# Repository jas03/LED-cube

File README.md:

# LED-cube
Design project for ECE-411

A 3x3x3 tricolor LED Cube that responds to music.

Members:

Evan Yand
Matthew Konyndyk
Alex Mendez
Jasjit Singh

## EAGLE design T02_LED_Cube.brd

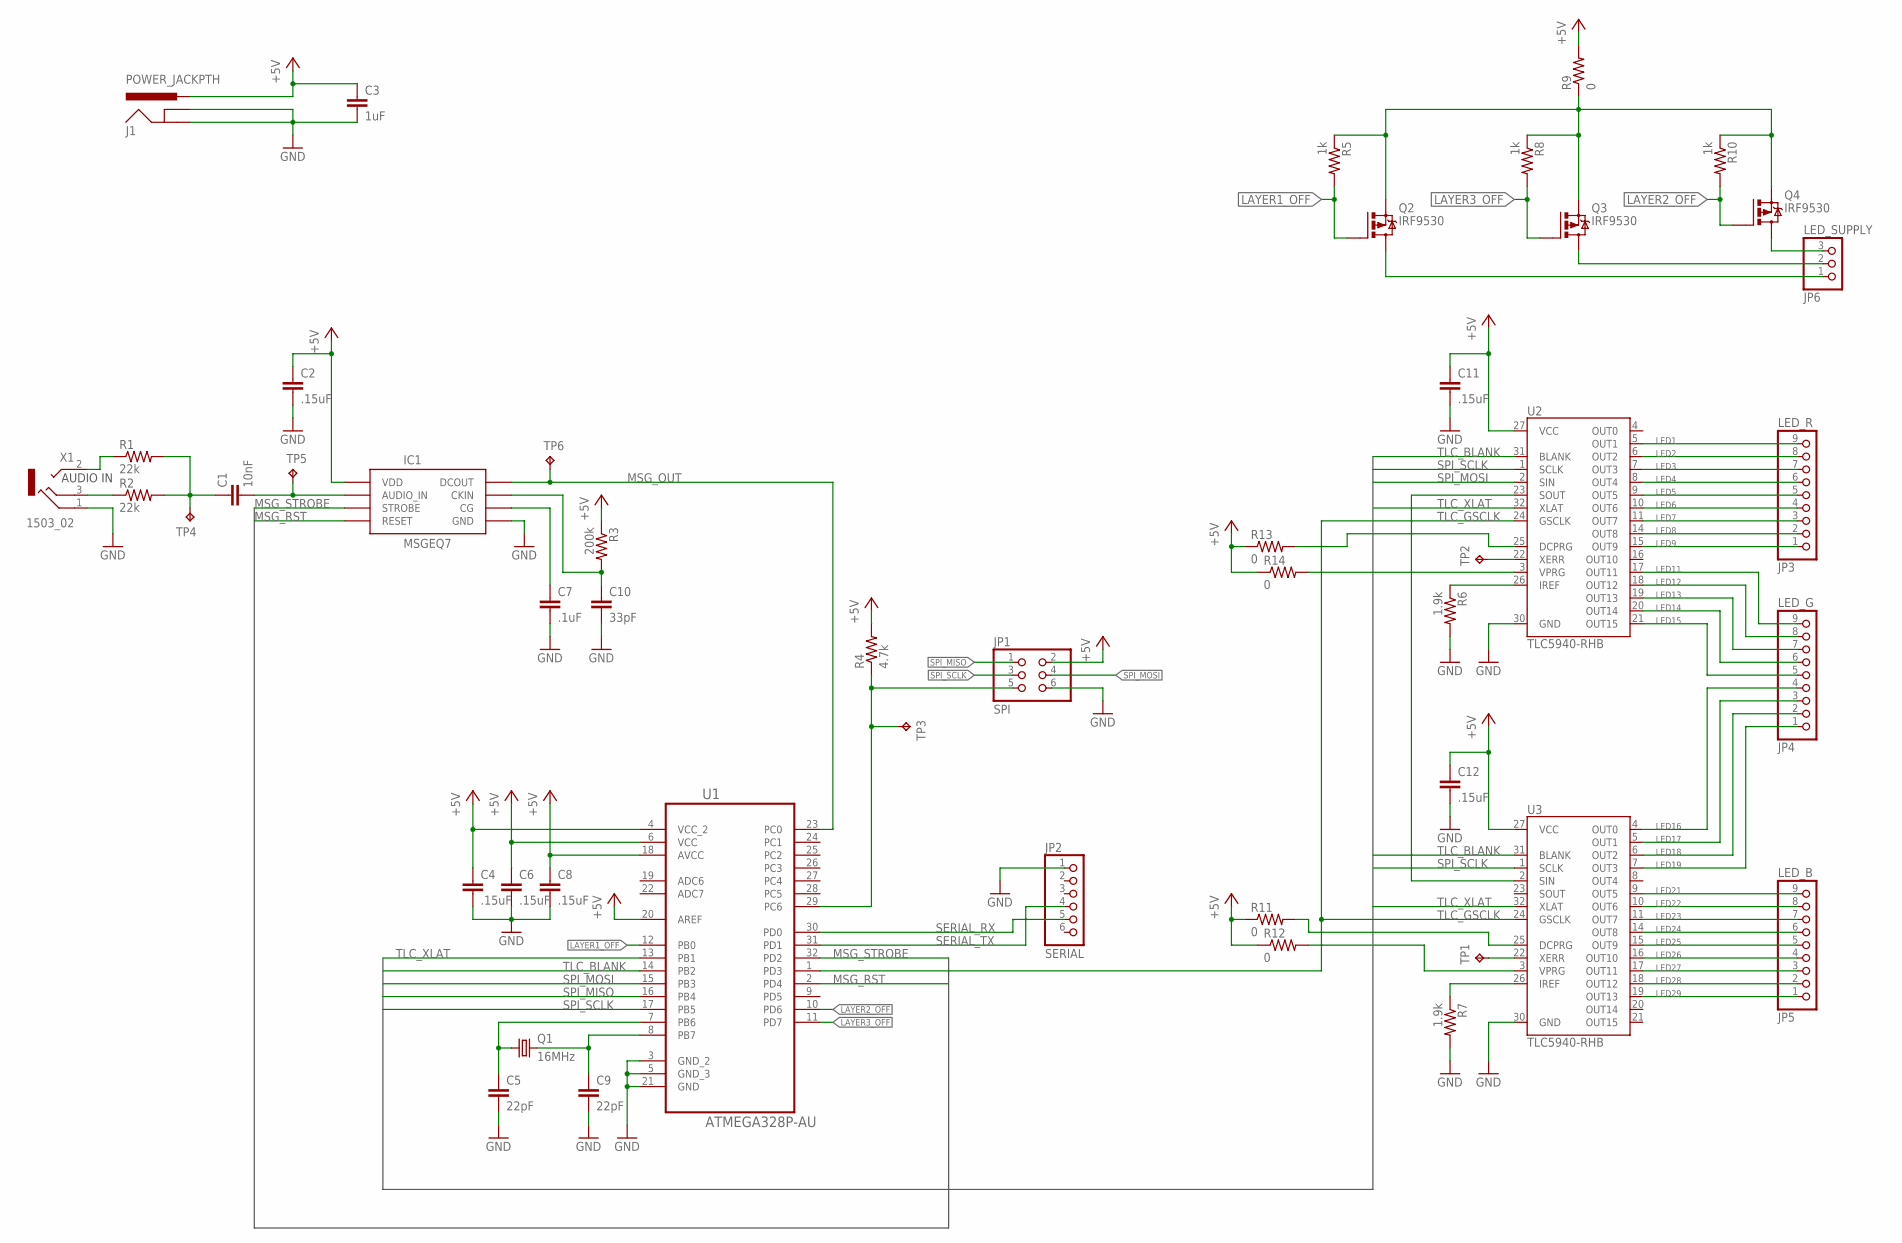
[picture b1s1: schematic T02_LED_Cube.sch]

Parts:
C1: 10nF; C0805
C2, C4, C6, C8, C11, C12: .15uF; C0402
C3: 1uF; C0805
C5, C9: 22pF; C0805
C7: .1uF; C0805
C10: 33pF; C0805
IC1: MSGEQ7SOIC; SOIC8
J1: POWER_JACKPTH; POWER_JACK_PTH
JP1: SPI; 2X03
JP2: SERIAL; 1X06
JP3: LED_R; 1X09
JP4: LED_G; 1X09
JP5: LED_B; 1X09
JP6: LED_SUPPLY; 1X03
Q1: 16MHz; HC49UP
Q2, Q3, Q4: IRF9530; TO220BV
R1, R2: 22k; R0805
R3: 200k; R0805
R4: 4.7k; R0805
R5, R8, R10: 1k; R0805
R6, R7: 1.9k; R0402
R9: 0; R1210
R11, R12, R13, R14: 0; R0402
TP1, TP2, TP3, TP4, TP5, TP6: TPPAD1-13; P1-13
U1: ATMEGA328P-AU; QFP80P900X900X120-32N
U2, U3: TLC5940-RHB; QFN-32
X1: 1503_02

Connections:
+5V: C2.1, C3.1, C4.1, C6.1, C8.1, C11.1, C12.1, IC1.1 (VDD), J1.PWR, JP1.2, R3.1, R4.2, R9.2, R11.1, R12.1, R13.1, R14.1, U1.4 (VCC_2), U1.6 (VCC), U1.18 (AVCC), U1.20 (AREF), U2.27 (VCC), U3.27 (VCC)
ATM_RST: JP1.5, R4.1, TP3.TP, U1.29 (PC6)
CRY_1: C5.1, Q1.1, U1.7 (PB6)
CRY_2: C9.1, Q1.2, U1.8 (PB7)
GND: C2.2, C3.2, C4.2, C5.2, C6.2, C7.2, C8.2, C9.2, C10.2, C11.2, C12.2, IC1.2 (GND), J1.GND, J1.GNDBREAK, JP1.6, JP2.1, R6.2, R7.2, U1.3 (GND_2), U1.5 (GND_3), U1.21 (GND), U2.30 (GND), U3.30 (GND), X1.1
LAY1_SUPPLY: JP6.1, Q2.D
LAY2_SUPPLY: JP6.3, Q4.D
LAY3_SUPPLY: JP6.2, Q3.D
LAYER1_OFF: Q2.G, R5.2, U1.12 (PB0)
LAYER2_OFF: Q4.G, R10.2, U1.10 (PD6)
LAYER3_OFF: Q3.G, R8.2, U1.11 (PD7)
LED1: JP3.9, U2.5 (OUT1)
LED2: JP3.8, U2.6 (OUT2)
LED3: JP3.7, U2.7 (OUT3)
LED4: JP3.6, U2.8 (OUT4)
LED5: JP3.5, U2.9 (OUT5)
LED6: JP3.4, U2.10 (OUT6)
LED7: JP3.3, U2.11 (OUT7)
LED8: JP3.2, U2.14 (OUT8)
LED9: JP3.1, U2.15 (OUT9)
LED11: JP4.9, U2.17 (OUT11)
LED12: JP4.8, U2.18 (OUT12)
LED13: JP4.7, U2.19 (OUT13)
LED14: JP4.6, U2.20 (OUT14)
LED15: JP4.5, U2.21 (OUT15)
LED16: JP4.4, U3.4 (OUT0)
LED17: JP4.3, U3.5 (OUT1)
LED18: JP4.2, U3.6 (OUT2)
LED19: JP4.1, U3.7 (OUT3)
LED21: JP5.9, U3.9 (OUT5)
LED22: JP5.8, U3.10 (OUT6)
LED23: JP5.7, U3.11 (OUT7)
LED24: JP5.6, U3.14 (OUT8)
LED25: JP5.5, U3.15 (OUT9)
LED26: JP5.4, U3.16 (OUT10)
LED27: JP5.3, U3.17 (OUT11)
LED28: JP5.2, U3.18 (OUT12)
LED29: JP5.1, U3.19 (OUT13)
LED_SUPPLY: Q2.S, Q3.S, Q4.S, R5.1, R8.1, R9.1, R10.1
MSG_CG: C7.1, IC1.6 (CG)
MSG_CKIN: C10.1, IC1.8 (CKIN), R3.2
MSG_INPUT: C1.2, IC1.5 (AUDIO_IN), TP5.TP
MSG_OUT: IC1.3 (DCOUT), TP6.TP, U1.23 (PC0)
MSG_RST: IC1.7 (RESET), U1.2 (PD4)
MSG_STROBE: IC1.4 (STROBE), U1.32 (PD2)
unnamed: R2.1, X1.3
unnamed: R1.1, X1.2
unnamed: R12.2, U3.3 (VPRG)
unnamed: R14.2, U2.3 (VPRG)
unnamed: R11.2, U3.25 (DCPRG)
unnamed: R13.2, U2.25 (DCPRG)
SERIAL_RX: JP2.5, U1.30 (PD0)
SERIAL_TX: JP2.4, U1.31 (PD1)
SPI_MISO: JP1.1, U1.16 (PB4)
SPI_MOSI: JP1.4, U1.15 (PB3), U2.2 (SIN)
SPI_SCLK: JP1.3, U1.17 (PB5), U2.1 (SCLK), U3.1 (SCLK)
TLC1_ERR: TP2.TP, U2.22 (XERR)
TLC1_IREF: R6.1, U2.26 (IREF)
TLC2_ERR: TP1.TP, U3.22 (XERR)
TLC2_IREF: R7.1, U3.26 (IREF)
TLC_BLANK: U1.14 (PB2), U2.31 (BLANK), U3.31 (BLANK)
TLC_CHAIN: U2.23 (SOUT), U3.2 (SIN)
TLC_GSCLK: U1.1 (PD3), U2.24 (GSCLK), U3.24 (GSCLK)
TLC_XLAT: U1.13 (PB1), U2.32 (XLAT), U3.32 (XLAT)
UNFILTERED_INPUT: C1.1, R1.2, R2.2, TP4.TP

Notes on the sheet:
AUDIO IN

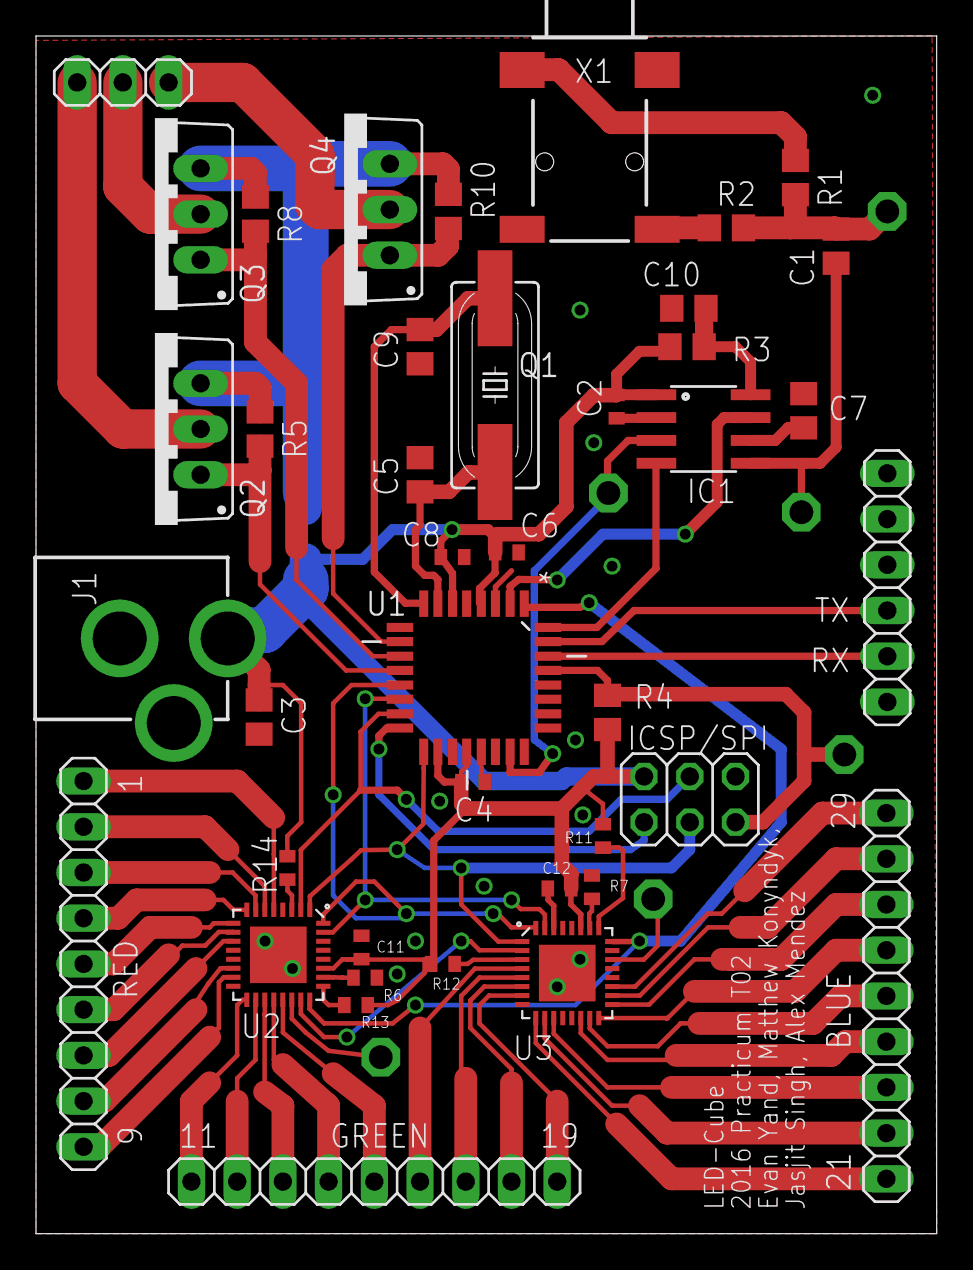
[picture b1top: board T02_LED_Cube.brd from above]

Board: 2 copper layers, 50.0 x 66.5 mm, 48 parts (1 on the bottom side), 65 nets.

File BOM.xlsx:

Part | Value | Device | Package | Description | Cost @ 500 units
Components
C1 | 10nF | C-EUC0805 | C0805 | Capacitor | 9.9000000000000008E-3
C2 | .15uF | C-EUC0402 | C0402 | Capacitor | 9.9000000000000008E-3
C3 | 1uF | C-EUC0805 | C0805 | Capacitor | 9.9000000000000008E-3
C4 | .15uF | C-EUC0402 | C0402 | Capacitor | 9.9000000000000008E-3
C5 | 22pF | C-EUC0805 | C0805 | Capacitor | 9.9000000000000008E-3
C6 | .15uF | C-EUC0402 | C0402 | Capacitor | 9.9000000000000008E-3
C7 | .1uF | C-EUC0805 | C0805 | Capacitor | 9.9000000000000008E-3
C8 | .15uF | C-EUC0402 | C0402 | Capacitor | 9.9000000000000008E-3
C9 | 22pF | C-EUC0805 | C0805 | Capacitor | 9.9000000000000008E-3
C10 | 33pF | C-EUC0805 | C0805 | Capacitor | 9.9000000000000008E-3
C11 | .15uF | C-EUC0402 | C0402 | Capacitor | 9.9000000000000008E-3
C12 | .15uF | C-EUC0402 | C0402 | Capacitor | 9.9000000000000008E-3
R1 | 22k | R-US_R0805 | R0805 | Resistor | 2.8999999999999998E-3
R2 | 22k | R-US_R0805 | R0805 | Resistor | 2.8999999999999998E-3
R3 | 200k | R-US_R0805 | R0805 | Resistor | 2.8999999999999998E-3
R4 | 4.7k | R-US_R0805 | R0805 | Resistor | 2.8999999999999998E-3
R5 | 1k | R-US_R0805 | R0805 | Resistor | 2.8999999999999998E-3
R6 | 1.9k | R-US_R0402 | R0402 | Resistor | 2.8999999999999998E-3
R7 | 1.9k | R-US_R0402 | R0402 | Resistor | 2.8999999999999998E-3
R8 | 1k | R-US_R0805 | R0805 | Resistor | 2.8999999999999998E-3
R9 | 0 | R-US_R1210 | R1210 | Resistor | 2.8999999999999998E-3
R10 | 1k | R-US_R0805 | R0805 | Resistor | 2.8999999999999998E-3
R11 | 0 | R-US_R0402 | R0402 | Resistor | 2.8999999999999998E-3
R12 | 0 | R-US_R0402 | R0402 | Resistor | 2.8999999999999998E-3
R13 | 0 | R-US_R0402 | R0402 | Resistor | 2.8999999999999998E-3
R14 | 0 | R-US_R0402 | R0402 | Resistor | 2.8999999999999998E-3
JP1 | SPI | PINHD-2X3 | 2X03 | Pin Header | 0.13420000000000001
JP2 | SERIAL | PINHD-1X6 | 1X06 | Pin Header | 0.69611999999999996
JP3 | LED_R | PINHD-1X9 | 1X09 | Pin Header
JP4 | LED_G | PINHD-1X9 | 1X09 | Pin Header |  | Not in Final Design
JP5 | LED_B | PINHD-1X9 | 1X09 | Pin Header
JP6 | LED_SUPPLY | PINHD-1X3 | 1X03 | Pin Header
Q1 | 16MHz | CRYSTALHC49UP | HC49UP | CRYSTAL | 0.15884000000000001
Q2 | IRF9530 | IRF9530 | TO220BV | P-Channel Power MOSFET | 0.79610000000000003
Q3 | IRF9530 | IRF9530 | TO220BV | P-Channel Power MOSFET | 0.79610000000000003
Q4 | IRF9530 | IRF9530 | TO220BV | P-Channel Power MOSFET | 0.79610000000000003
IC1 | MSGEQ7SOIC | MSGEQ7SOIC | SOIC8 | 7-band Graphic equalizer | 4.46
U1 | ATMEGA328P-AU | ATMEGA328P-AU | QFP80P-32N | 8-bit Microcontroller | 2.2605200000000001
U2 | TLC5940-RHB | TLC5940-RHB | QFN-32 | 16-channel LED Driver | 1.76986
U3 | TLC5940-RHB | TLC5940-RHB | QFN-32 | 16-channel LED Driver | 1.76986
X1 | 1503_02 | 1503_02 | 1503_02 | 3.5mm Jack | 0.63558000000000003
J1 | POWER_JACKPTH | POWER_JACKPTH | POWER_JACK_PTH | Power | 0.81774000000000002
Additional Parts
PCB |  |  |  |  | 5
Case - Acrylic |  |  |  |  | 0.8
Case - Plastic |  |  |  |  | 2
DC Power Supply |  |  |  |  | 5.07
RGB LEDs | Qty:27 |  | 0.06 |  | 1.6199999999999999
Additional Wire | Qty:15 in |  |  |  | 2.75
 |  |  |  | Total: | 29.74042
 |  |  | Estimate @ 10000 Units: |  | 14.87021

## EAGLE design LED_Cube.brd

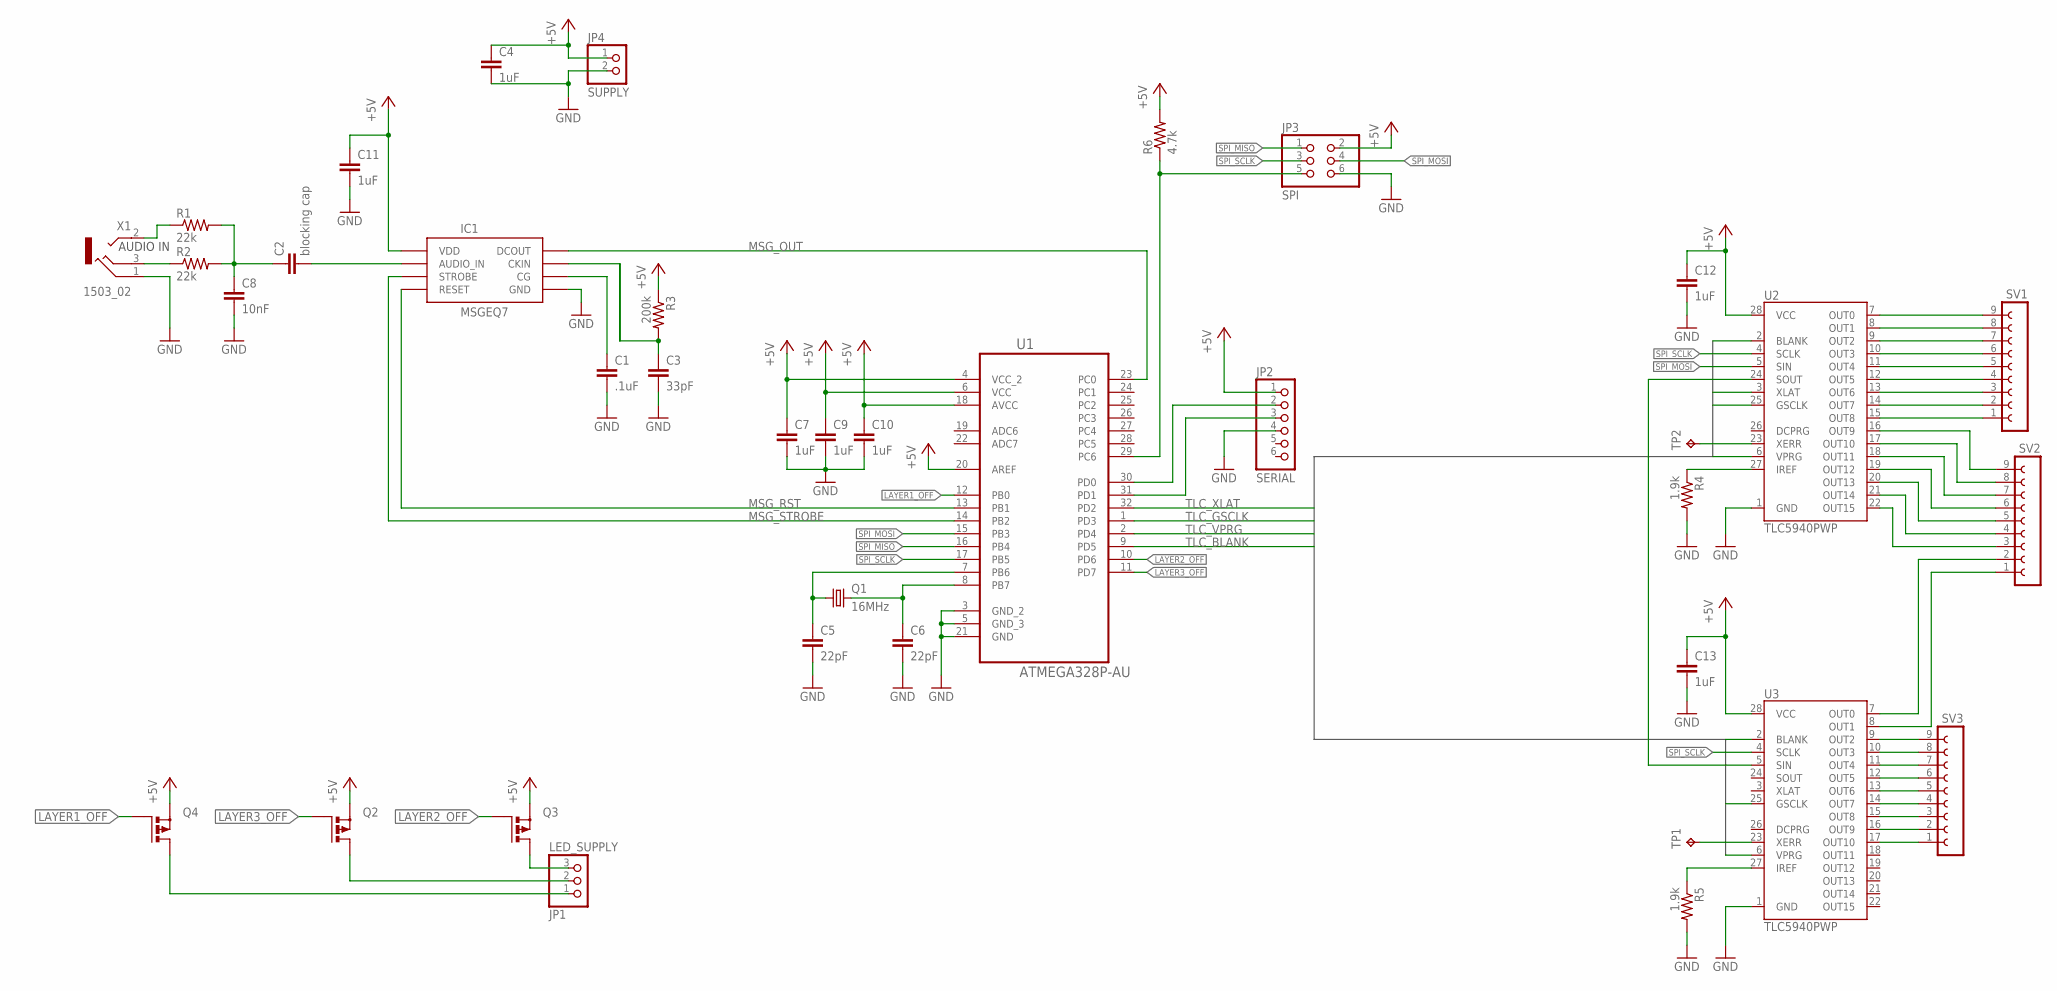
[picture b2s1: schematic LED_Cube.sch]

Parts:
C1: .1uF; C0805
C2: blocking cap; C0805
C3: 33pF; C0805
C4, C7, C9, C10, C11, C12, C13: 1uF; C0805
C5, C6: 22pF; C0805
C8: 10nF; C0805
IC1: MSGEQ7SOIC; SOIC8
JP1: LED_SUPPLY; 1X03
JP2: SERIAL; 1X06
JP3: SPI; 2X03
JP4: SUPPLY; 1X02
Q1: 16MHz; HC49UP
Q2, Q3, Q4: PMOSFET_PTO220BH; TO220BH
R1, R2: 22k; R0805
R3: 200k; R0805
R4, R5: 1.9k; R0805
R6: 4.7k; R0805
SV1, SV2, SV3: FE09-1; FE09
TP1, TP2: TPPAD1-13; P1-13
U1: ATMEGA328P-AU; QFP80P900X900X120-32N
U2, U3: TLC5940PWP; TSSOP28-GROUNDPAD
X1: 1503_02

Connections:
+5V: C4.1, C7.1, C9.1, C10.1, C11.1, C12.1, C13.1, IC1.1 (VDD), JP2.1, JP3.2, JP4.1, Q2.S, Q3.S, Q4.S, R3.1, R6.2, U1.4 (VCC_2), U1.6 (VCC), U1.18 (AVCC), U1.20 (AREF), U2.28 (VCC), U3.28 (VCC)
ATM_RST: JP3.5, R6.1, U1.29 (PC6)
CRY_1: C5.1, Q1.1, U1.7 (PB6)
CRY_2: C6.1, Q1.2, U1.8 (PB7)
GND: C1.2, C3.2, C4.2, C5.2, C6.2, C7.2, C8.2, C9.2, C10.2, C11.2, C12.2, C13.2, IC1.2 (GND), JP2.4, JP3.6, JP4.2, R4.2, R5.2, U1.3 (GND_2), U1.5 (GND_3), U1.21 (GND), U2.1 (GND), U3.1 (GND), X1.1
LAY2_SUPPLY: JP1.3, Q3.D
LAY3_SUPPLY: JP1.2, Q2.D
LAY4_SUPPLY: JP1.1, Q4.D
LAYER1_OFF: Q4.G, U1.12 (PB0)
LAYER2_OFF: Q3.G, U1.10 (PD6)
LAYER3_OFF: Q2.G, U1.11 (PD7)
MSG_CG: C1.1, IC1.6 (CG)
MSG_CKIN: C3.1, IC1.8 (CKIN), R3.2
MSG_INPUT: C2.2, IC1.5 (AUDIO_IN)
MSG_OUT: IC1.3 (DCOUT), U1.23 (PC0)
MSG_RST: IC1.7 (RESET), U1.13 (PB1)
MSG_STROBE: IC1.4 (STROBE), U1.14 (PB2)
unnamed: R2.1, X1.3
unnamed: R1.1, X1.2
unnamed: SV1.6, U2.10 (OUT3)
unnamed: SV1.9, U2.7 (OUT0)
unnamed: SV1.8, U2.8 (OUT1)
unnamed: SV1.7, U2.9 (OUT2)
unnamed: SV1.5, U2.11 (OUT4)
unnamed: SV1.4, U2.12 (OUT5)
unnamed: SV1.3, U2.13 (OUT6)
unnamed: SV1.2, U2.14 (OUT7)
unnamed: SV3.1, U3.17 (OUT10)
unnamed: SV1.1, U2.15 (OUT8)
unnamed: SV3.2, U3.16 (OUT9)
unnamed: SV3.3, U3.15 (OUT8)
unnamed: SV3.4, U3.14 (OUT7)
unnamed: SV3.5, U3.13 (OUT6)
unnamed: SV3.6, U3.12 (OUT5)
unnamed: SV3.7, U3.11 (OUT4)
unnamed: SV3.8, U3.10 (OUT3)
unnamed: SV3.9, U3.9 (OUT2)
unnamed: SV2.1, U3.8 (OUT1)
unnamed: SV2.2, U3.7 (OUT0)
unnamed: SV2.9, U2.16 (OUT9)
unnamed: SV2.8, U2.17 (OUT10)
unnamed: SV2.7, U2.18 (OUT11)
unnamed: SV2.6, U2.19 (OUT12)
unnamed: SV2.5, U2.20 (OUT13)
unnamed: SV2.4, U2.21 (OUT14)
unnamed: SV2.3, U2.22 (OUT15)
unnamed: JP2.2, U1.30 (PD0)
unnamed: U2.24 (SOUT), U3.5 (SIN)
unnamed: JP2.3, U1.31 (PD1)
unnamed: R5.1, U3.27 (IREF)
unnamed: R4.1, U2.27 (IREF)
SPI_MISO: JP3.1, U1.16 (PB4)
SPI_MOSI: JP3.4, U1.15 (PB3), U2.5 (SIN)
SPI_SCLK: JP3.3, U1.17 (PB5), U2.4 (SCLK), U3.4 (SCLK)
TLC1_ERR: TP2.TP, U2.23 (XERR)
TLC2_ERR: TP1.TP, U3.23 (XERR)
TLC_BLANK: U1.9 (PD5), U2.2 (BLANK), U3.2 (BLANK)
TLC_GSCLK: U1.1 (PD3), U2.25 (GSCLK), U3.25 (GSCLK)
TLC_VPRG: U1.2 (PD4), U2.6 (VPRG), U3.6 (VPRG)
TLC_XLAT: U1.32 (PD2), U2.3 (XLAT)
UNFILTERED_INPUT: C2.1, C8.1, R1.2, R2.2

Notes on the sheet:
AUDIO IN

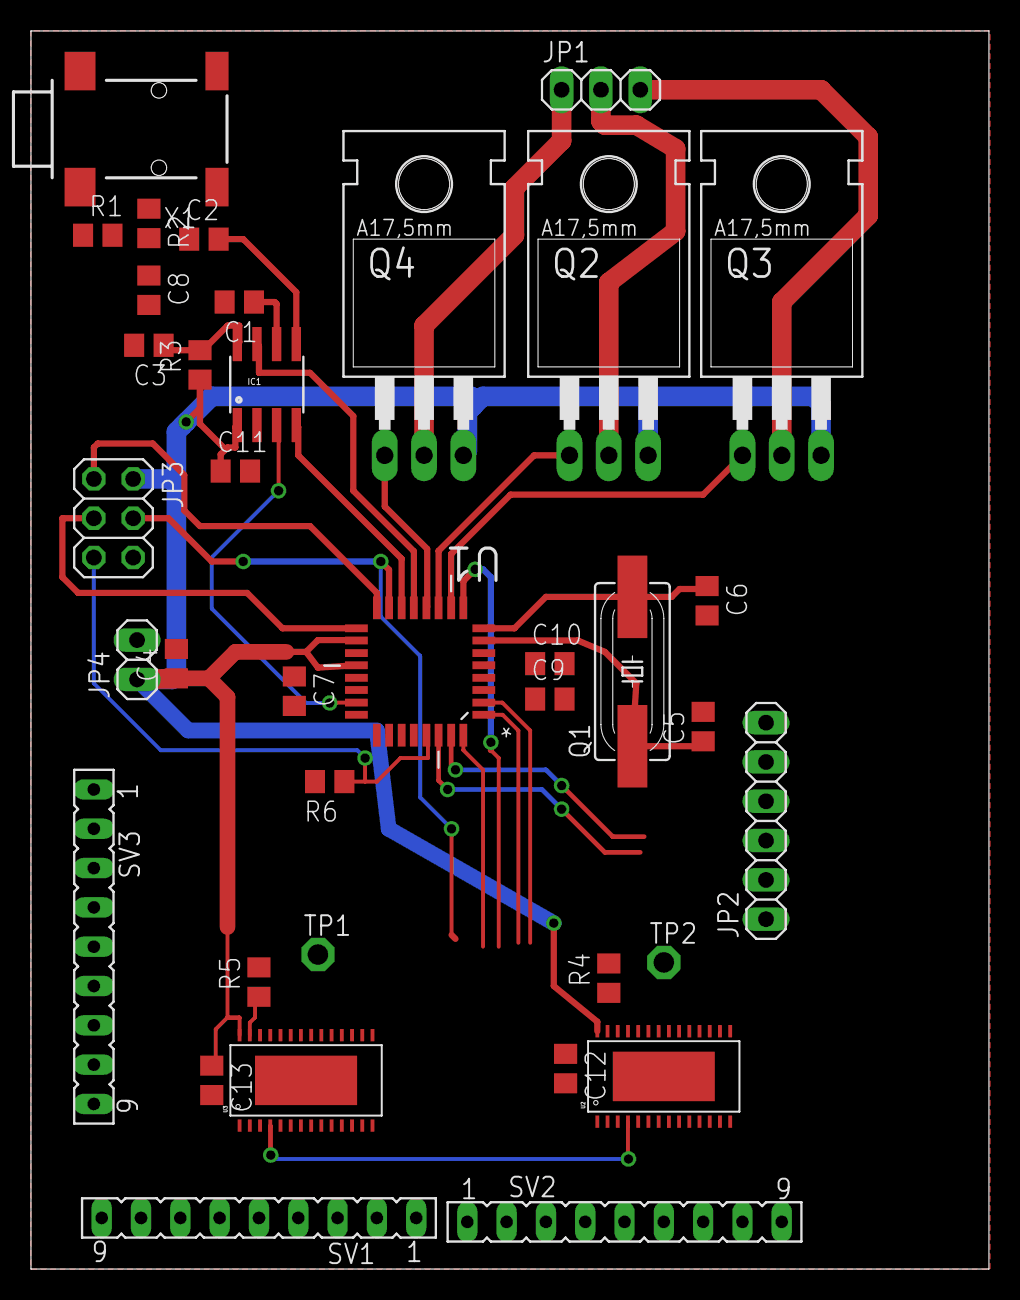
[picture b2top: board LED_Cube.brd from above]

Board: 2 copper layers, 61.9 x 80.0 mm, 37 parts (0 on the bottom side), 61 nets.

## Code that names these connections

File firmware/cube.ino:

#include <tlc_shifts.h>
#include <tlc_servos.h>
#include <tlc_animations.h>
#include <tlc_fades.h>
#include <tlc_progmem_utils.h>
#include <tlc_config.h>
#include <Tlc5940.h>


//Pin Definitions
#define TLC_SIN    1
#define TLC_SCLK   2
#define TLC_GSCLK  2
#define TLC_XLAT   2
#define TLC_BLANK  2
#define TLC_VPRG   2

#define MSG_OUT    3
#define MSG_STRBE  2
#define MSG_RST    2

#define LYR1       2
#define LYR2       2
#define LYR3       2


//Vars
int audio[7]    //7 byte array for audio data


//Code
void setup(){


    digitalWrite(LYR2, HIGH);
    digitalWrite(LYR3, HIGH);
    digitalWrite(LYR1, HIGH);



    //Pin Setup
    pinMode(TLC_SIN, OUTPUT);
    pinMode(TLC_SCLK, OUTPUT);
    pinMode(TLC_GSCLK, OUTPUT);
    pinMode(TLC_XLAT, OUTPUT);
    pinMode(TLC_BLANK, OUTPUT);
    pinMode(TLC_VPRG, OUTPUT);

    pinMode(MSG_RST, OUTPUT);
    pinMode(MSG_STRBE, OUTPUT);
   

    //System Initialization
    digitalWrite(TLC_BLANK, HIGH);

}




void loop(){

    //Check audio
    checkMSG();

    //Set Layer 1
    setLayer(LYR1);

    //Output pattern for layer 1

    //Set Layer 2
    setLayer(LYR2);

    //Output pattern for layer 2

    //Set Layer 3
    setLayer(LYR3);

    //Output pattern for layer 3

}

//Functions

void setLayer(int lay){
    //Currently uses digitalWrite() which may be too slow

    if(lay == LYR1){

        digitalWrite(LYR2, HIGH);
        digitalWrite(LYR3, HIGH);
        digitalWrite(LYR1, LOW);

    }

    if(lay == LYR2){

        digitalWrite(LYR1, HIGH);
        digitalWrite(LYR3, HIGH);
        digitalWrite(LYR2, LOW);

    }

    if(lay == LYR3){

        digitalWrite(LYR2, HIGH);
        digitalWrite(LYR1, HIGH);
        digitalWrite(LYR3, LOW);

    }

}

void checkMSG(){
    //Scans each channel and writes out to an array

    //Reset to channel 1
    digitalWrite(MSG_RST, HIGH);
    digitalWrite(MSG_RST, LOW);

    for(int band=0; band <7; band++)
    {
        digitalWrite(MSG_STRBE, LOW);           // strobe pin on the shield - kicks the IC up to the next band
        delayMicroseconds(30);                  //This needs to be dealt with (interrupts?)
        left[band] = analogRead(MSG_OUT);       // store left band reading

        digitalWrite(MSG_STRBE, HIGH);
     }
}

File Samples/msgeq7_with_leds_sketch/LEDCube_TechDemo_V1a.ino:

/*
 * Alex Mendez
 * Portland State University
 * ECE 411
 * October 30, 2016
 * 
 * Description:
 * This program takes an audio input and splits the audio signal into 7
 * bands that each control a distinct portion of a 3x3x3 LED cube. The
 * strength of each band dictates the brightness of the lights. This is
 * currently a tech demo and does not resemble the final product.
 */

#include "Tlc5940.h"

#define LayerOne 6      // PD6 (pin 11 of chip)
#define LayerTwo 7      //  PD7 (pin 12 of chip)
#define LayerThree 8    //   PB0 (pin 13 of chip)

#define analogPin 0     // read from multiplexer using analog input 0
#define strobePin 2     // strobe is attached to digital pin 2
#define resetPin 4      // reset is attached to digital pin 3
#define THRESH 65       // threshold level
int spectrumValue[7];   // to hold a2d values

/*
 * To turn off a layer:

PORT_ |= _BV(___);  //layer 1

To turn on a layer:

PORT_ &= ~_BV(___);  //layer 1

where

_ = 'B' 'C' or 'D' depending on the pin

___ = the pin name
 * To turn off a layer:

PORTD |= _BV(PD6);  //layer 1

To turn on a layer:

PORTD &= ~_BV(PD6);  //layer 1
*/

void setup()
{

 //msg setup
 Serial.begin(9600);
 pinMode(analogPin, INPUT);
 pinMode(strobePin, OUTPUT);
 pinMode(resetPin, OUTPUT);
 analogReference(DEFAULT);

 digitalWrite(resetPin, LOW);
 digitalWrite(strobePin, HIGH);


 //tlc setup
 pinMode(LayerOne, OUTPUT);
 pinMode(LayerTwo, OUTPUT);
 pinMode(LayerThree, OUTPUT);
  
 Tlc.init();
/*
PORTD &= _BV(PD6);  //layer 1
PORTD &= _BV(PD7);  //layer 2
PORTB &= _BV(PB0);  //layer 3
*/
 digitalWrite(LayerOne, LOW);
 digitalWrite(LayerTwo, LOW);
 digitalWrite(LayerThree, LOW); 
}

void loop()
{
//PORTD |= ~_BV(PD4);  //reset high
//delayMicroseconds(20);
//PORTD &= _BV(PD4);  //reset low
 digitalWrite(resetPin, HIGH);
 digitalWrite(resetPin, LOW);

 for (int i = 0; i < 7; i++)
 {

//PORTD &= _BV(PD2);  //strobe low
 digitalWrite(strobePin, LOW);
 delayMicroseconds(26); // to allow the output to settle
 spectrumValue[i] = analogRead(analogPin);


 if ((i<=1) && (spectrumValue[i]>THRESH)) 
      Tlc.set(i+9,3*spectrumValue[i]);
 else
      Tlc.set(i+9, 0);
 if ((i<=5) && (spectrumValue[i]>THRESH))
      Tlc.set(i+20,3*spectrumValue[i]);
  else
      Tlc.set(i+20, 0);
 if ((i<=7) && (spectrumValue[i]>THRESH))
      Tlc.set(i+2,3*spectrumValue[i]);
  else
      Tlc.set(i+2, 0);
 Tlc.update();

//PORTD |= _BV(PD2);  //strobe high
//delayMicroseconds(30);
 digitalWrite(strobePin, HIGH);
 }
}

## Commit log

2016-10-06 RGB LED datasheet
    The attached datasheet should help us understand the RGB LEDs a bit more and how they can be controlled.
2016-10-08 MSGEQ7 datasheet
    The datasheet for the Seven Band Graphic Equalizer
2016-10-08 schematic Rev 0
2016-10-08 MSGEQ7 Set up
2016-10-08 Datasheets folder addition
    Just shoving the LEDs into a new folder for easier reference
2016-10-08 1/3 TLC5940 set up
2016-10-13 began ATMEGA integration into schemaic. Specified tenative pins
2016-10-13 further atmega connections
2016-10-15 Schematic almost done
2016-10-17 more schematic
2016-10-23 schematic & board updated
2016-10-23 new board [15%]
2016-10-23 schematic 80%/board 25%
2016-10-23 schematic 80%/board 35%
2016-10-27 Update of Sample Codes
2016-10-29 started template for firmware
2016-10-29 more outlining of code
2016-10-29 sketched MSGEQ7 read function
2016-10-30 More Suff
2016-10-30 Added test.ino, which integrates the entire system
2016-10-31 LED Cube Proof of Concept
    This program should show how our LED cube is going to work, using a basic pattern to demonstrate how the LED cube can be controlled by an audio signal.
2016-11-01 prelim schematic done. second draft of board [50%]
2016-11-03 renamed files with prefix; added busses to sch
2016-11-05 pcb 75% done
2016-11-14 board 95% besides stitching
2016-11-17 submitted board
2016-11-17 fixed some text
2016-12-09 Coding
    Adding folders with our coded programs
2016-12-09 Edits
2016-12-09 Added BOM

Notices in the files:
parts and their libraries:
SparkFun-DigitalIC: Licensing: Creative Commons ShareAlike 4.0 International - https://creativecommons.org/licenses/by-sa/4.0
